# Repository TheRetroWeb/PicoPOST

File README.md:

# PicoPOST

> [!NOTE]
> You can get a quick summary from the blog post! [Introducing the PicoPOST - The Retro Web Blog](https://blog.theretroweb.com/2023/01/03/introducing-the-picopost/)

## Introduction

**PicoPOST** is a PC diagnostic card for systems with, at least, an 8-bit ISA slot. It's based around the Raspberry Pi
Pico, powered by an RP2040.

PicoPOST is designed to provide many additional benefits over the basic POST cards that are commonly available from
Chinese vendors on eBay and other sites.

This project is getting ready for public usage, with a few prototypes already in use for development purposes. More
information soon as it gets finalized.

## Implemented features

- Simple user interface, with a graphical monochrome 128x32 OLED display and a few buttons living on their own remote
  control
- Port 80h readout, with 4-place output history
- Port 90h readout, for IBM PS/2s
- Port 84h reaodut, for Compaq machines*
- Port 300h readout, for some EISA systems*
- Port 378h readout, for some Olivetti machines*
- More complete bus activity dumping facility
- Reset pulse detection
- +5V and +12V ~~and -12V~~ voltage monitor**
- Display is dimmed after 15s of inactivity to mitigate burn-in
- Flying Toasters! screensaver after 30s of inactivity on the main menu

> *: We don't have a specimen handy, so we need confirmation from someone else out there.\
> **: Negative voltages into a positive ADC is too much mental gymnastics without additional hardware

### Videos

We are slowly compiling a [YouTube playlist](https://www.youtube.com/playlist?list=PLejCJef6DKnVJob0ycztrpl9FoBufaOPA)
with a whole bunch of demonstration pieces, showing what the PicoPOST is capable of doing.\
Stay tuned for more content!

### Wishlist

New features have been implemented with the new rev 6 PCB and matching firmware.
- Full bus activity trace (HW OK, FW provisioned, but we need to make sure we are not missing data)
- Bus clock reader (HW OK, FW TBD)
- ... anything else, as long as the hardware allows it and someone implements it in firmware

## Building the firmware

### Automagically

We make use of Visual Studio Code and the official Raspberry Pi Pico extension for an easier life. When you first open
the project in VSCode, you will be prompted to install a few suggested extensions; accept the proposal and follow
on-screen instructions.

You should now be greeted by the CMake and Pi Pico sidebar panels. Use the CMake panel to switch between Debug or
Release builds, then refer to the Pico panel for building, uploading, and debugging the firmware.

It's already set up to probe for a compatible debugger via OpenOCD and gdbserver, and it works really well with our
official Raspberry Pi Debug Probe. I expect other SWD debuggers to work just as well (J-Link, STLink, ...).

### Manually

The firmware is built using the official Raspberry Pi RP2040 SDK. Follow the
[official documentation](https://github.com/raspberrypi/pico-sdk#quick-start-your-own-project) for setting it up.

The procedure is pretty straight-forward:
1. Clone the repo
   ```
   mkdir ~/repo
   cd ~/repo
   git clone https://github.com/TheRetroWeb/PicoPOST
   ```
2. Enter the repo and initialize it
   ```
   cd PicoPOST
   git submodule init
   git submodule update
   ```
3. Prepare the build system with CMake
   ```
   export PICO_SDK_PATH /path/to/pico/sdk
   cmake -DCMAKE_EXPORT_COMPILE_COMMANDS:BOOL=TRUE \
       -DCMAKE_BUILD_TYPE:STRING=Release \
       -DCMAKE_C_COMPILER:FILEPATH=/usr/bin/arm-none-eabi-gcc \
       -DCMAKE_CXX_COMPILER:FILEPATH=/usr/bin/arm-none-eabi-g++ \
       -S./firmware \
       -B./build \
       -G "Unix Makefiles"
   ```
4. Build the firmware
   ```
   cmake --build ./build --config Release --target all -j $(nproc)
   ```

### Customize the firmware

There are a couple of details you might want to tune at compile time. More specifically, you may want to better calibrate
the voltage monitor to show more accurate results.

In the primary `firmware\CMakeLists.txt` file, there are three variables you can set to skew the final ADC conversion result. These were added to account for resistor tolerances in the voltage divider circuits.
- `CALIBADJ_5V`, correction factor for the +5V rail
- `CALIBADJ_12V`, correction factor for the +12V rail

Calculating these factors is pretty straight forward:
- Install the default firmware
- Connect PicoPOST to your computer of choice with a known good power supply
- Enter `Voltage Monitor` mode
- Turn on the computer
- With a multimeter, measure the rail voltage as close as possible to PicoPOST
- Compute the required calibration factor by dividing the measured value with the one shown by PicoPOST
- Edit the `CALIBADJ` variable and build the firmware again

## Flashing the firmware

1. In order to load new firmware, the Pico must be booted into UF2 mode:
   - If the board is powered off, keep the BOOTSEL button pressed while plugging the USB cable into the Pico itself.
   - If the board is already powered, you can short the "Pico Reset" pins on the back of the card instead of removing the USB cable.
   - Alternatively, if the board is powered via USB from a PC with a data cable, you can move to the `Update FW` menu entry. By pressing Enter, the Pico will then be rebooted into UF2 mode automatically.
2. A mass storage device should be now mounted on your computer.
3. Drag and drop (or copy and paste) the `.uf2` firmware file into the device.
4. Once loaded, it will automatically restart and disconnect.
5. If all went well, you should now be greeted by the main menu on the OLED display.\
   You can verify the current firmware version by entering the `Info` page.

## Interested in helping?
- Submit issues and pull requests!
- Join us in the #picopost channel in [The Retro Web discord server](https://discord.gg/TdD4tqQ7fv)
- Join us and other developers of retro Pico hardware (such as PicoGUS and PicoMEM) in the [Retro Pico Hardware discord server](https://discord.gg/QBUkpPqFa5)

## Directories

```
datasheets/  Reference documentation for components used in the PicoPOST
firmware/    Source code for the PicoPOST firmware (written in C/C++ with the official Pico SDK)
pcb/         KiCad schematics and PCB design files
```

## License

The firmware portion of PicoPOST is licensed under the MIT license.\
The hardware portion of PicoPOST is licensed under the CERN OHL v2 Permissive license.

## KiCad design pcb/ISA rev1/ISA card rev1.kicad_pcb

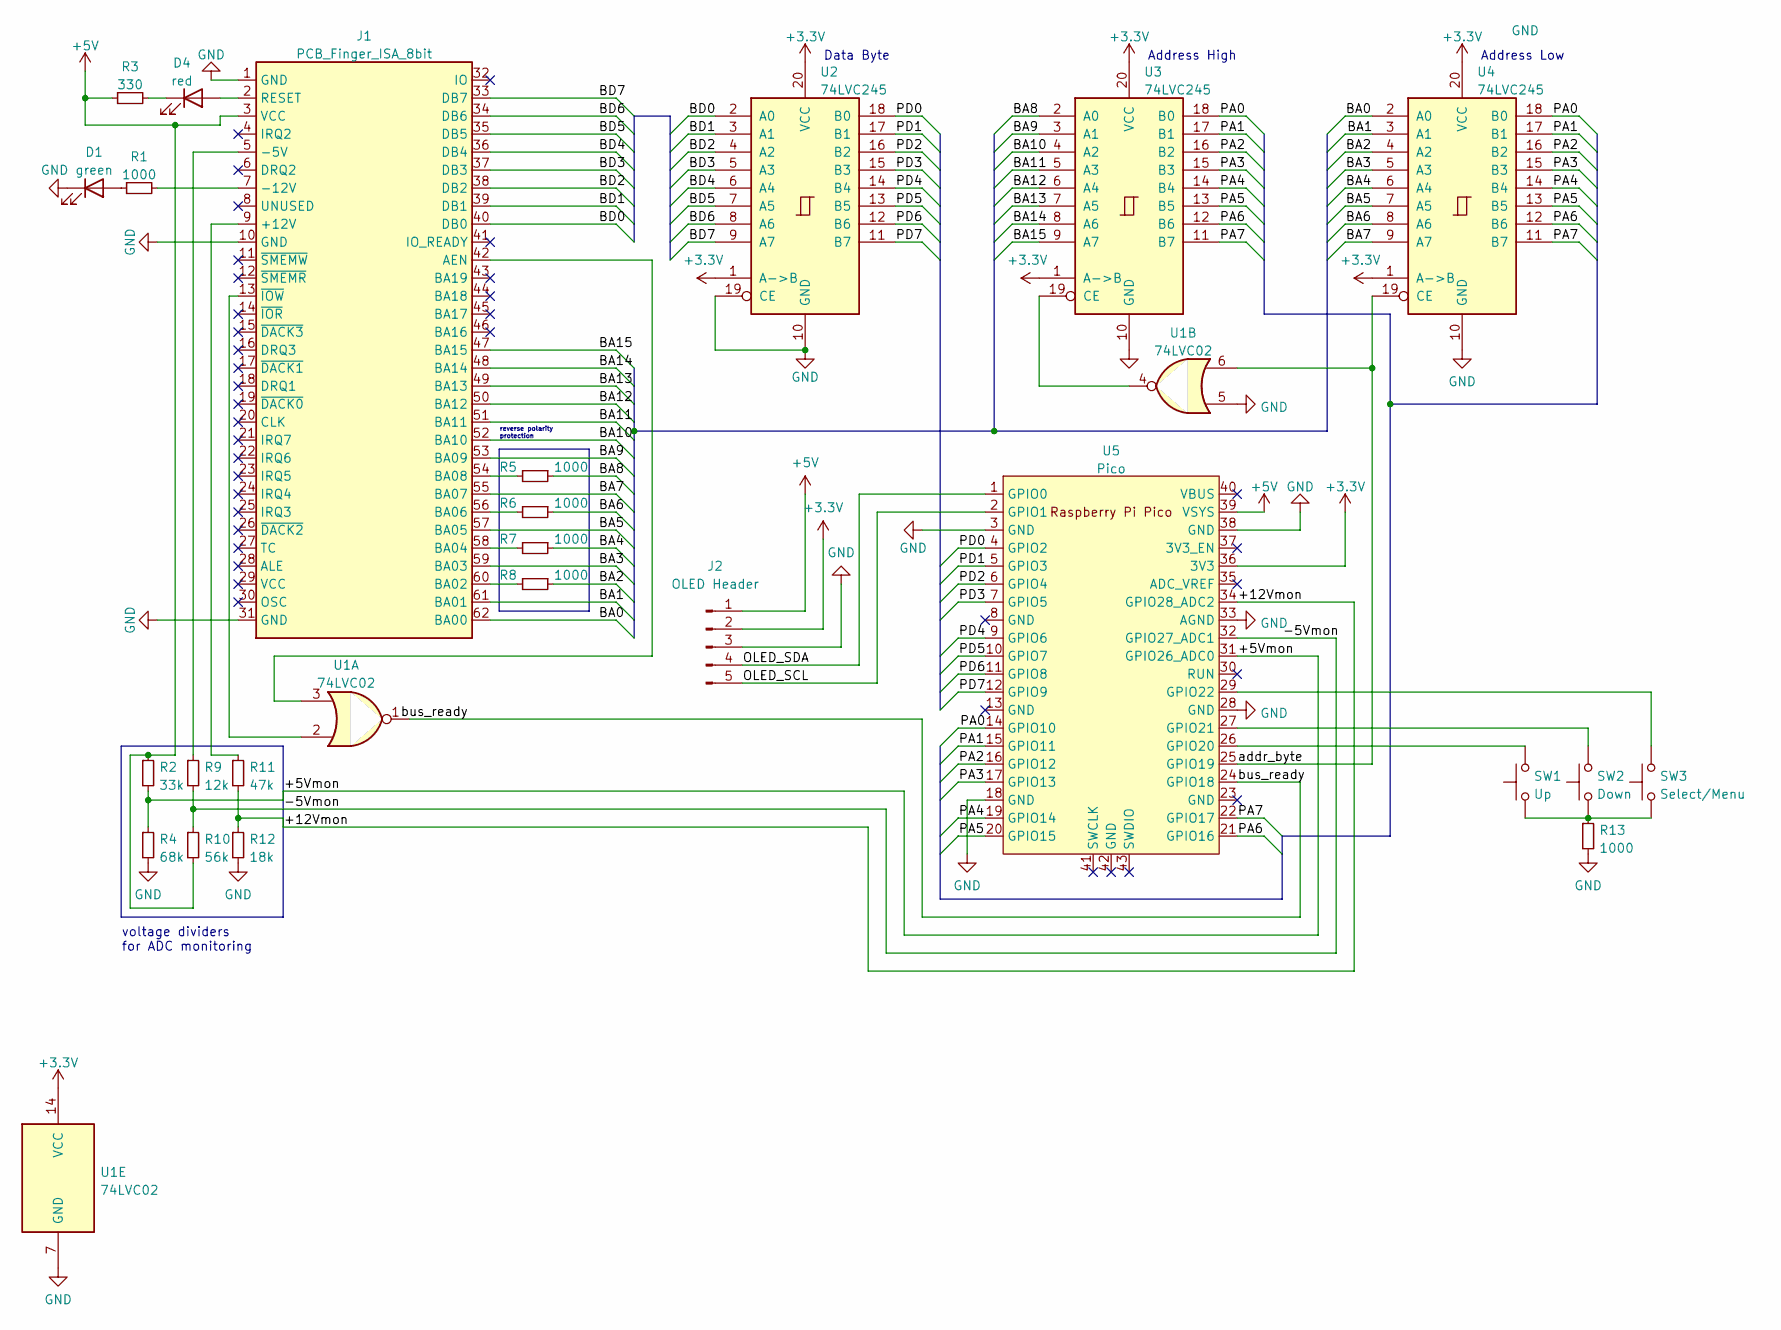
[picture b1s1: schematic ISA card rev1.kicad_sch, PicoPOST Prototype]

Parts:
D1: green; LED_D3.0mm
D4: red; LED_D3.0mm
J1: PCB_Finger_ISA_8bit; BUS_IDE8
J2: OLED Header; PinHeader_1x05_P2.54mm_Vertical
R1, R5, R6, R7, R8, R13: 1000; R_Axial_DIN0207_L6.3mm_D2.5mm_P2.54mm_Vertical
R2: 33k; R_Axial_DIN0207_L6.3mm_D2.5mm_P2.54mm_Vertical
R3: 330; R_Axial_DIN0207_L6.3mm_D2.5mm_P2.54mm_Vertical
R4: 68k; R_Axial_DIN0207_L6.3mm_D2.5mm_P2.54mm_Vertical
R9: 12k; R_Axial_DIN0207_L6.3mm_D2.5mm_P2.54mm_Vertical
R10: 56k; R_Axial_DIN0207_L6.3mm_D2.5mm_P2.54mm_Vertical
R11: 47k; R_Axial_DIN0207_L6.3mm_D2.5mm_P2.54mm_Vertical
R12: 18k; R_Axial_DIN0207_L6.3mm_D2.5mm_P2.54mm_Vertical
SW1: Up; SW_PUSH_6mm_H5mm
SW2: Down; SW_PUSH_6mm_H5mm
SW3: Select/Menu; SW_PUSH_6mm_H5mm
U1: 74LVC02; SO-14_5.3x10.2mm_P1.27mm
U2, U3, U4: 74LVC245; SO-20_5.3x12.6mm_P1.27mm
U5: Pico; RPi_Pico_SMD_TH

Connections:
+3V3: J2.2, U1.14 (VCC), U2.1 (A->B), U2.20 (VCC), U3.1 (A->B), U3.20 (VCC), U4.1 (A->B), U4.20 (VCC), U5.36 (3V3)
+5V: J1.3 (VCC), J2.1, R2.1, R3.1, R10.2, U5.39 (VSYS)
/+5Vmon: R2.2, R4.1, U5.31 (GPIO26_ADC0)
/+12Vmon: R11.2, R12.1, U5.34 (GPIO28_ADC2)
/-5Vmon: R9.2, R10.1, U5.32 (GPIO27_ADC1)
/BA0: J1.62 (BA00), U4.2 (A0)
/BA1: J1.61 (BA01), U4.3 (A1)
/BA2: R8.1, U4.4 (A2)
/BA3: J1.59 (BA03), U4.5 (A3)
/BA4: R7.1, U4.6 (A4)
/BA5: J1.57 (BA05), U4.7 (A5)
/BA6: R6.1, U4.8 (A6)
/BA7: J1.55 (BA07), U4.9 (A7)
/BA8: R5.1, U3.2 (A0)
/BA9: J1.53 (BA09), U3.3 (A1)
/BA10: J1.52 (BA10), U3.4 (A2)
/BA11: J1.51 (BA11), U3.5 (A3)
/BA12: J1.50 (BA12), U3.6 (A4)
/BA13: J1.49 (BA13), U3.7 (A5)
/BA14: J1.48 (BA14), U3.8 (A6)
/BA15: J1.47 (BA15), U3.9 (A7)
/BD0: J1.40 (DB0), U2.2 (A0)
/BD1: J1.39 (DB1), U2.3 (A1)
/BD2: J1.38 (DB2), U2.4 (A2)
/BD3: J1.37 (DB3), U2.5 (A3)
/BD4: J1.36 (DB4), U2.6 (A4)
/BD5: J1.35 (DB5), U2.7 (A5)
/BD6: J1.34 (DB6), U2.8 (A6)
/BD7: J1.33 (DB7), U2.9 (A7)
/OLED_SCL: J2.5, U5.2 (GPIO1)
/OLED_SDA: J2.4, U5.1 (GPIO0)
/PA0: U3.18 (B0), U4.18 (B0), U5.14 (GPIO10)
/PA1: U3.17 (B1), U4.17 (B1), U5.15 (GPIO11)
/PA2: U3.16 (B2), U4.16 (B2), U5.16 (GPIO12)
/PA3: U3.15 (B3), U4.15 (B3), U5.17 (GPIO13)
/PA4: U3.14 (B4), U4.14 (B4), U5.19 (GPIO14)
/PA5: U3.13 (B5), U4.13 (B5), U5.20 (GPIO15)
/PA6: U3.12 (B6), U4.12 (B6), U5.21 (GPIO16)
/PA7: U3.11 (B7), U4.11 (B7), U5.22 (GPIO17)
/PD0: U2.18 (B0), U5.4 (GPIO2)
/PD1: U2.17 (B1), U5.5 (GPIO3)
/PD2: U2.16 (B2), U5.6 (GPIO4)
/PD3: U2.15 (B3), U5.7 (GPIO5)
/PD4: U2.14 (B4), U5.9 (GPIO6)
/PD5: U2.13 (B5), U5.10 (GPIO7)
/PD6: U2.12 (B6), U5.11 (GPIO8)
/PD7: U2.11 (B7), U5.12 (GPIO9)
/addr_byte: U1.6, U4.19 (CE), U5.25 (GPIO19)
/bus_ready: U1.1, U5.24 (GPIO18)
GND: D1.1 (K), J1.1 (GND), J1.10 (GND), J1.31 (GND), J2.3, R4.2, R12.2, R13.2, U1.5, U1.7 (GND), U2.10 (GND), U2.19 (CE), U3.10 (GND), U4.10 (GND), U5.3 (GND), U5.18 (GND), U5.28 (GND), U5.33 (AGND), U5.38 (GND)
unnamed: D1.2 (A), R1.1
unnamed: D4.1 (K), R3.2
unnamed: D4.2 (A), J1.2 (RESET)
unnamed: J1.5 (-5V), R9.1
unnamed: J1.7 (-12V), R1.2
unnamed: J1.9 (+12V), R11.1
unnamed: J1.13 (~IOW), U1.2
unnamed: J1.42 (AEN), U1.3
unnamed: J1.54 (BA08), R5.2
unnamed: J1.56 (BA06), R6.2
unnamed: J1.58 (BA04), R7.2
unnamed: J1.60 (BA02), R8.2
unnamed: R13.1, SW1.1, SW2.1, SW3.1
unnamed: U1.4, U3.19 (CE)
unnamed: SW1.2, U5.26 (GPIO20)
unnamed: SW2.2, U5.27 (GPIO21)
unnamed: SW3.2, U5.29 (GPIO22)

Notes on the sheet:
reverse polarity protection
Data Byte
Address High
Address Low
voltage dividers for ADC monitoring

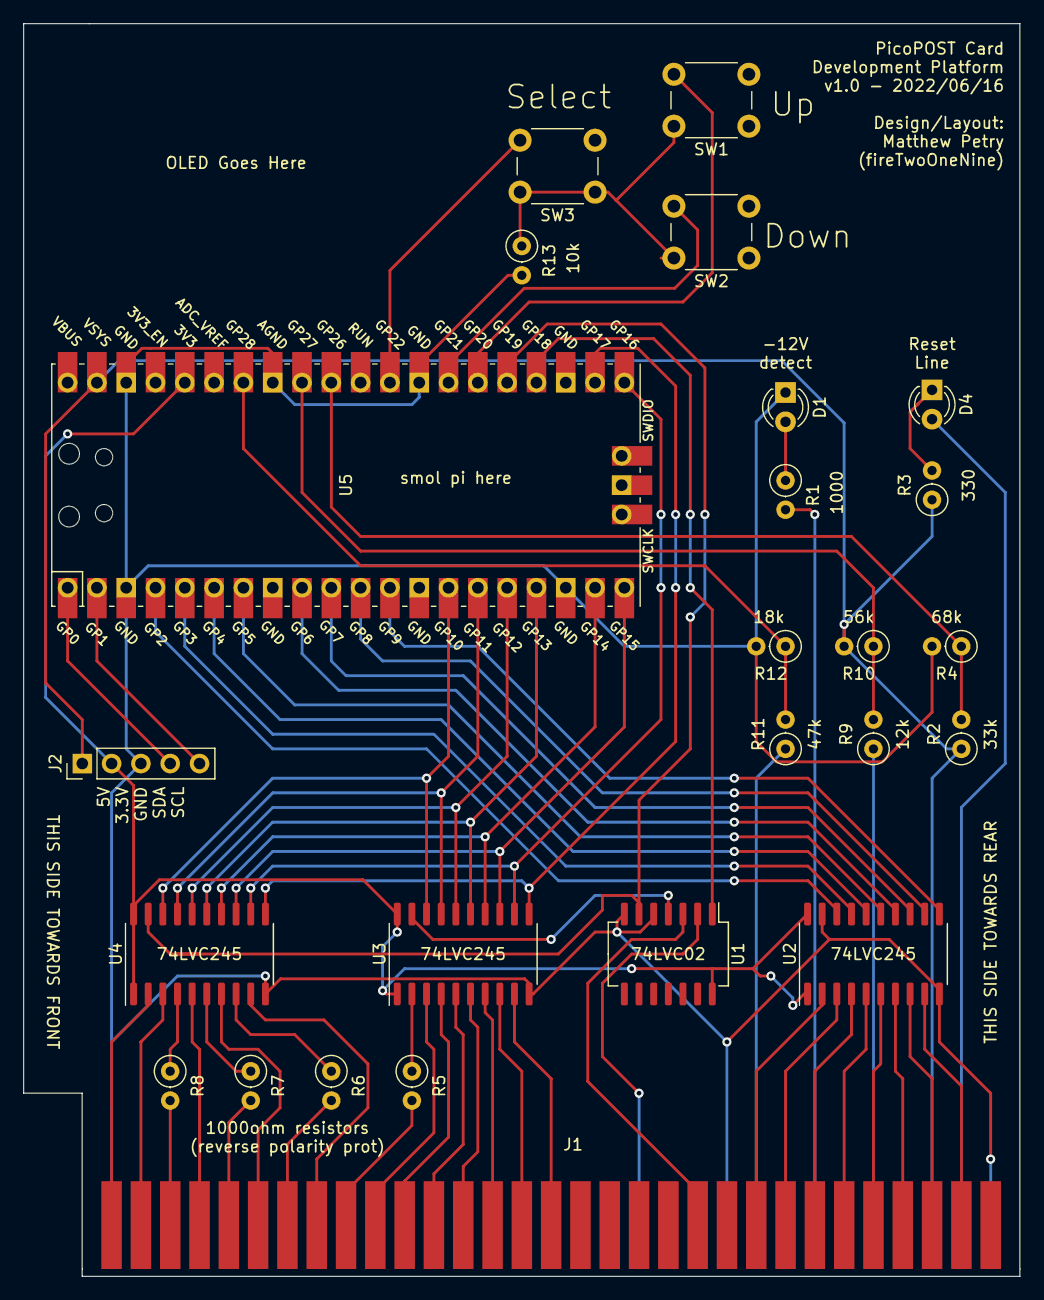
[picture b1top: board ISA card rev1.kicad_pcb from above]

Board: 2 copper layers, 86.4 x 108.6 mm, 25 parts (0 on the bottom side), 67 nets.

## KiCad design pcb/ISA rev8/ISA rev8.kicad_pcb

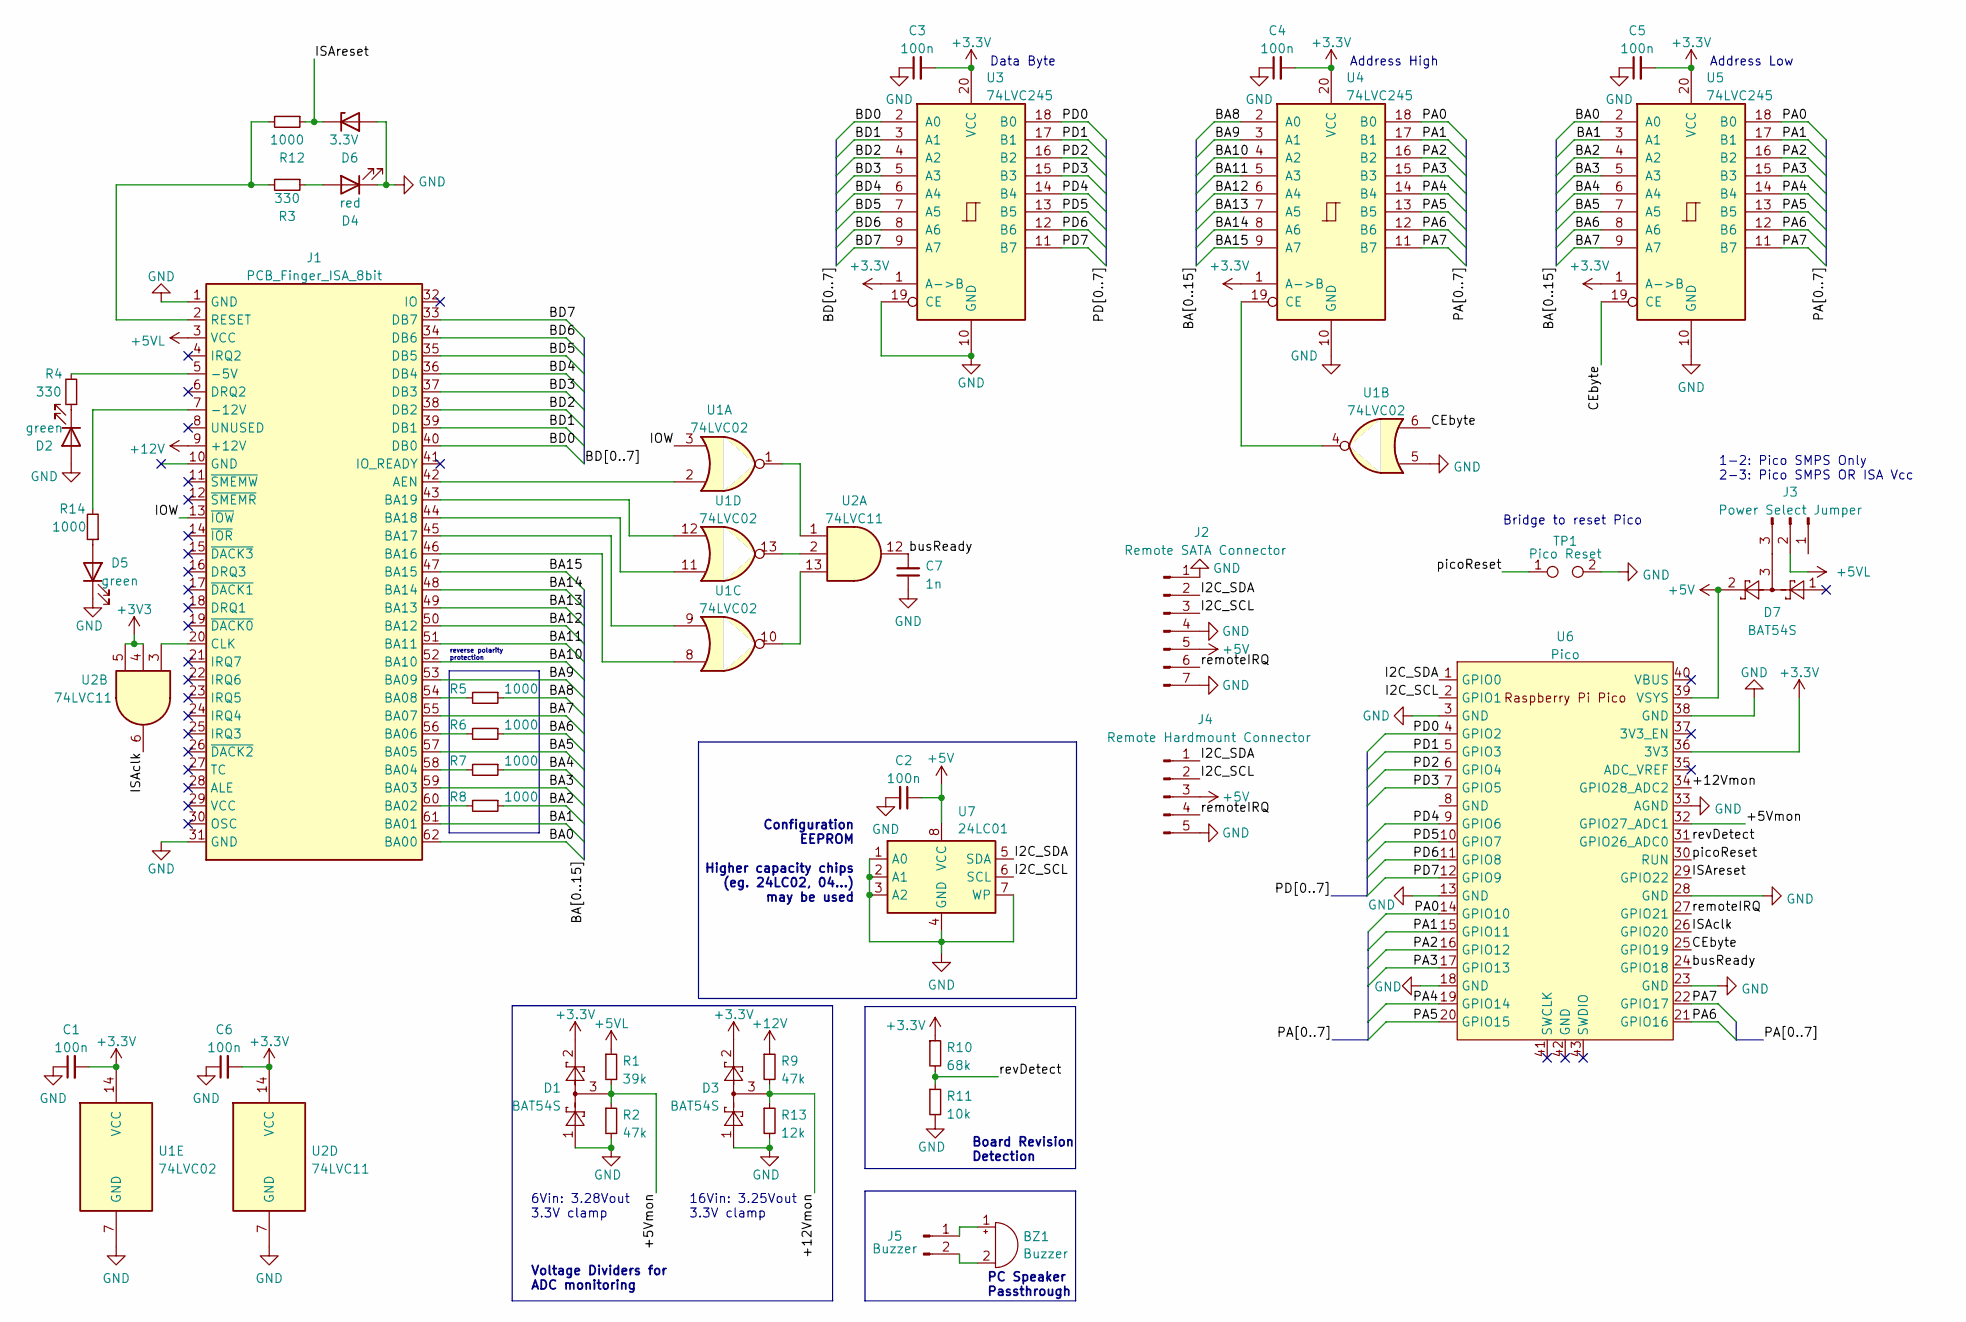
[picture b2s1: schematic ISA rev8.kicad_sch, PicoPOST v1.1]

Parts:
BZ1: Buzzer; 7.6mm side mount buzzer
C1, C2, C3, C4, C5, C6: 100n; C_1206_3216Metric_Pad1.33x1.80mm_HandSolder
C7: 1n; C_1206_3216Metric_Pad1.33x1.80mm_HandSolder
D1, D3, D7: BAT54S; SOT-23_Handsoldering
D2, D5: green; LED_D3.0mm
D4: red; LED_D3.0mm
D6: 3.3V; TO-236AB_diode
J1: PCB_Finger_ISA_8bit; BUS_IDE8
J2: Remote SATA Connector; Molex-47080-4001-0-0-0
J3: Power Select Jumper; PinHeader_1x03_P2.54mm_Vertical
J4: Remote Hardmount Connector; PinHeader_1x05_P2.54mm_Horizontal
J5: Buzzer; PinHeader_1x02_P2.54mm_Vertical
R1: 39k; R_1206_3216Metric_Pad1.30x1.75mm_HandSolder
R2, R9: 47k; R_1206_3216Metric_Pad1.30x1.75mm_HandSolder
R3, R4: 330; R_1206_3216Metric_Pad1.30x1.75mm_HandSolder
R5, R6, R7, R8, R12, R14: 1000; R_1206_3216Metric_Pad1.30x1.75mm_HandSolder
R10: 68k; R_1206_3216Metric_Pad1.30x1.75mm_HandSolder
R11: 10k; R_1206_3216Metric_Pad1.30x1.75mm_HandSolder
R13: 12k; R_1206_3216Metric_Pad1.30x1.75mm_HandSolder
TP1: Pico Reset; 6mm single side button
U1: 74LVC02; SO-14_3.9x8.65mm_P1.27mm
U2: 74LVC11; SO-14_3.9x8.65mm_P1.27mm
U3, U4, U5: 74LVC245; SO-20_5.3x12.6mm_P1.27mm
U6: Pico; RPi_Pico_SMD_TH
U7: 24LC01; SOIC-8_3.9x4.9mm_P1.27mm

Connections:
+5V: C2.1, D7.2, J2.5, J4.3, U6.39 (VSYS), U7.8 (VCC)
+5VL: J1.3 (VCC), J3.2, R1.1
+12V: J1.9 (+12V), R9.1
/+5Vmon: D1.3, R1.2, R2.1, U6.32 (GPIO27_ADC1)
/+12Vmon: D3.3, R9.2, R13.1, U6.34 (GPIO28_ADC2)
/BA0: J1.62 (BA00), U5.2 (A0)
/BA1: J1.61 (BA01), U5.3 (A1)
/BA2: R8.1, U5.4 (A2)
/BA3: J1.59 (BA03), U5.5 (A3)
/BA4: R7.1, U5.6 (A4)
/BA5: J1.57 (BA05), U5.7 (A5)
/BA6: R6.1, U5.8 (A6)
/BA7: J1.55 (BA07), U5.9 (A7)
/BA8: R5.1, U4.2 (A0)
/BA9: J1.53 (BA09), U4.3 (A1)
/BA10: J1.52 (BA10), U4.4 (A2)
/BA11: J1.51 (BA11), U4.5 (A3)
/BA12: J1.50 (BA12), U4.6 (A4)
/BA13: J1.49 (BA13), U4.7 (A5)
/BA14: J1.48 (BA14), U4.8 (A6)
/BA15: J1.47 (BA15), U4.9 (A7)
/BD0: J1.40 (DB0), U3.2 (A0)
/BD1: J1.39 (DB1), U3.3 (A1)
/BD2: J1.38 (DB2), U3.4 (A2)
/BD3: J1.37 (DB3), U3.5 (A3)
/BD4: J1.36 (DB4), U3.6 (A4)
/BD5: J1.35 (DB5), U3.7 (A5)
/BD6: J1.34 (DB6), U3.8 (A6)
/BD7: J1.33 (DB7), U3.9 (A7)
/CEbyte: U1.6, U5.19 (CE), U6.25 (GPIO19)
/I2C_SCL: J2.3, J4.2, U6.2 (GPIO1), U7.6 (SCL)
/I2C_SDA: J2.2, J4.1, U6.1 (GPIO0), U7.5 (SDA)
/IOW: J1.13 (~IOW), U1.3
/ISAclk: U2.6, U6.26 (GPIO20)
/ISAreset: D6.1 (K), R12.1, U6.29 (GPIO22)
/PA0: U4.18 (B0), U5.18 (B0), U6.14 (GPIO10)
/PA1: U4.17 (B1), U5.17 (B1), U6.15 (GPIO11)
/PA2: U4.16 (B2), U5.16 (B2), U6.16 (GPIO12)
/PA3: U4.15 (B3), U5.15 (B3), U6.17 (GPIO13)
/PA4: U4.14 (B4), U5.14 (B4), U6.19 (GPIO14)
/PA5: U4.13 (B5), U5.13 (B5), U6.20 (GPIO15)
/PA6: U4.12 (B6), U5.12 (B6), U6.21 (GPIO16)
/PA7: U4.11 (B7), U5.11 (B7), U6.22 (GPIO17)
/PD0: U3.18 (B0), U6.4 (GPIO2)
/PD1: U3.17 (B1), U6.5 (GPIO3)
/PD2: U3.16 (B2), U6.6 (GPIO4)
/PD3: U3.15 (B3), U6.7 (GPIO5)
/PD4: U3.14 (B4), U6.9 (GPIO6)
/PD5: U3.13 (B5), U6.10 (GPIO7)
/PD6: U3.12 (B6), U6.11 (GPIO8)
/PD7: U3.11 (B7), U6.12 (GPIO9)
/busReady: C7.2, U2.12, U6.24 (GPIO18)
/picoReset: TP1.1, U6.30 (RUN)
/remoteIRQ: J2.6, J4.4, U6.27 (GPIO21)
/revDetect: R10.2, R11.1, U6.31 (GPIO26_ADC0)
GND: C1.1, C2.2, C3.1, C4.1, C5.1, C6.1, C7.1, D1.1, D2.2 (A), D3.1, D4.1 (K), D5.1 (K), D6.2 (A), J1.1 (GND), J1.31 (GND), J2.1, J2.4, J2.7, J4.5, R2.2, R11.2, R13.2, TP1.2, U1.5, U1.7 (GND), U2.7 (GND), U3.10 (GND), U3.19 (CE), U4.10 (GND), U5.10 (GND), U6.3 (GND), U6.13 (GND), U6.18 (GND), U6.23 (GND), U6.28 (GND), U6.33 (AGND), U6.38 (GND), U7.1 (A0), U7.2 (A1), U7.3 (A2), U7.4 (GND), U7.7 (WP)
unnamed: BZ1.2 (+), J5.2
unnamed: BZ1.1 (-), J5.1
unnamed: D2.1 (K), R4.1
unnamed: D4.2 (A), R3.1
unnamed: D5.2 (A), R14.1
unnamed: J1.5 (-5V), R4.2
unnamed: J1.7 (-12V), R14.2
unnamed: J1.42 (AEN), U1.2
unnamed: J1.60 (BA02), R8.2
unnamed: J1.58 (BA04), R7.2
unnamed: J1.56 (BA06), R6.2
unnamed: J1.54 (BA08), R5.2
unnamed: J1.46 (BA16), U1.8
unnamed: J1.45 (BA17), U1.9
unnamed: J1.44 (BA18), U1.11
unnamed: J1.43 (BA19), U1.12
unnamed: J1.20 (CLK), U2.3
unnamed: J1.2 (RESET), R3.2, R12.2
unnamed: D7.3, J3.3
unnamed: U1.1, U2.1
unnamed: U1.10, U2.13
unnamed: U1.13, U2.2
unnamed: U1.4, U4.19 (CE)

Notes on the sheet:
6Vin: 3.28Vout 3.3V clamp
Configuration EEPROM Higher capacity chips (eg. 24LC02, 04...) may be used
Board Revision Detection
Voltage Dividers for ADC monitoring
reverse polarity protection
Data Byte
Bridge to reset Pico
Address High
1-2: Pico SMPS Only 2-3: Pico SMPS OR ISA Vcc
PC Speaker Passthrough
Address Low
16Vin: 3.25Vout 3.3V clamp

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
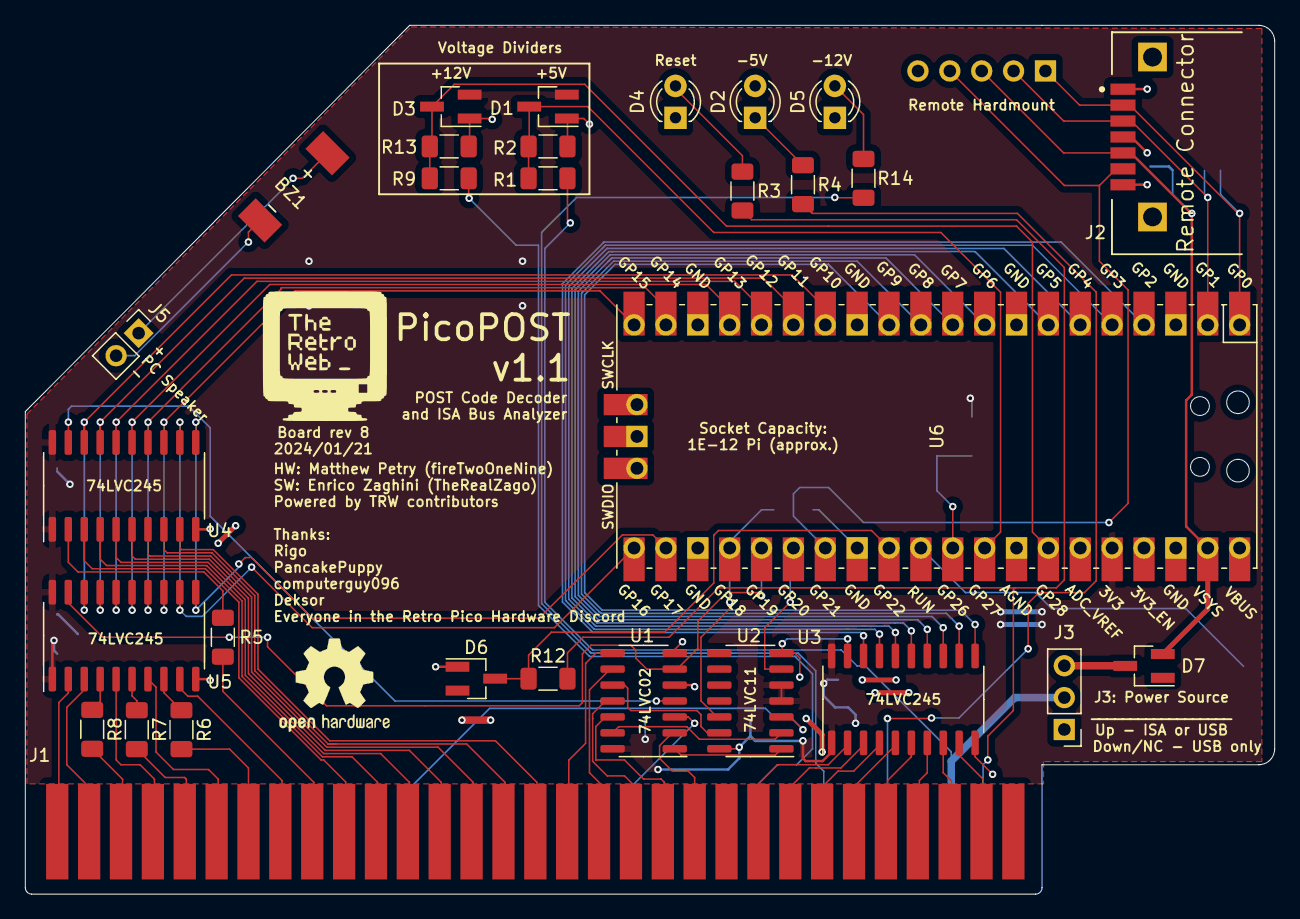
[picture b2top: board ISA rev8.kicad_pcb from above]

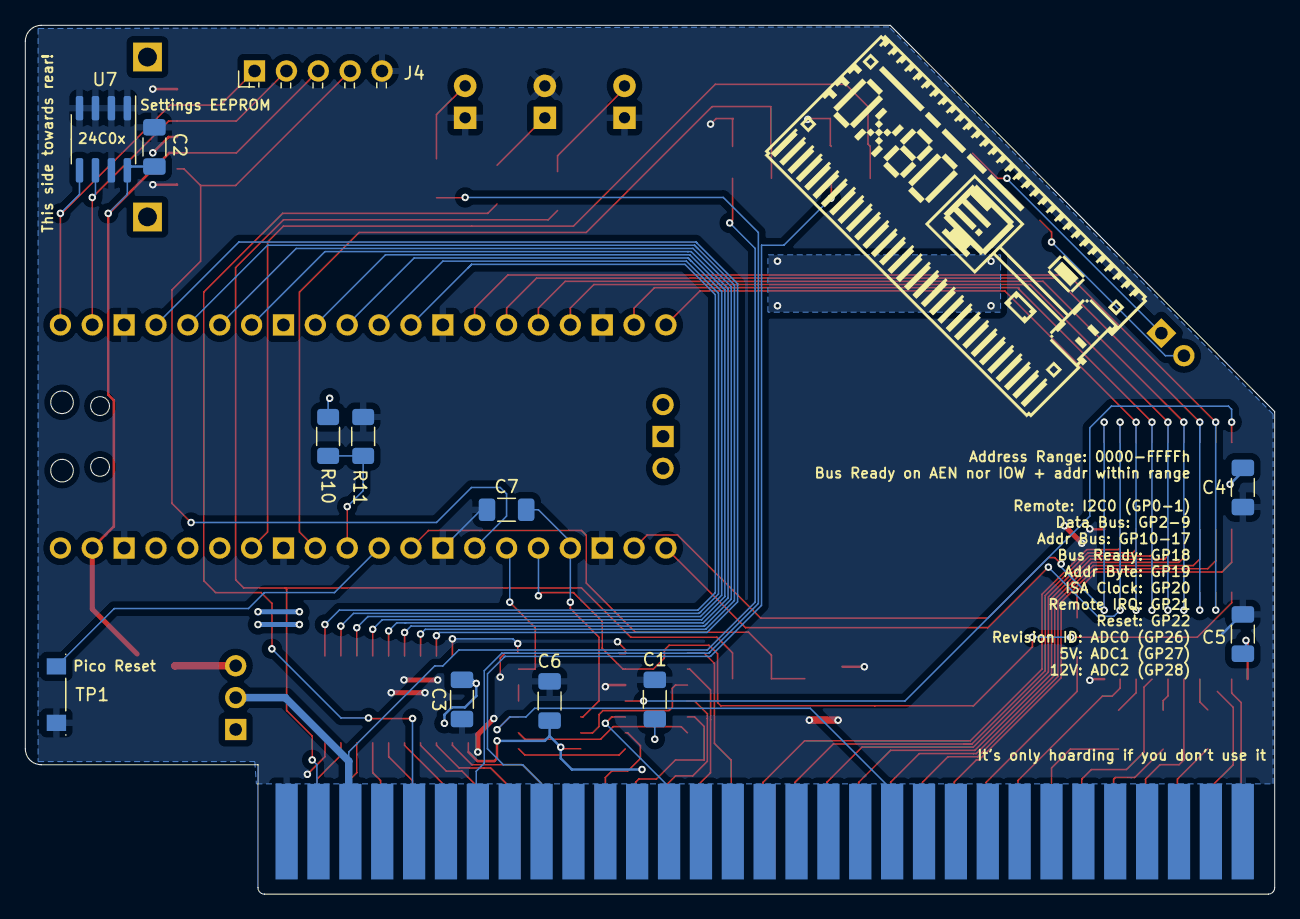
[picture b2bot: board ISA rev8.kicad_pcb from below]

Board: 2 copper layers, 99.6 x 69.2 mm, 43 parts (13 on the bottom side), 80 nets.

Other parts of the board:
.: LOGO; picopost_logo

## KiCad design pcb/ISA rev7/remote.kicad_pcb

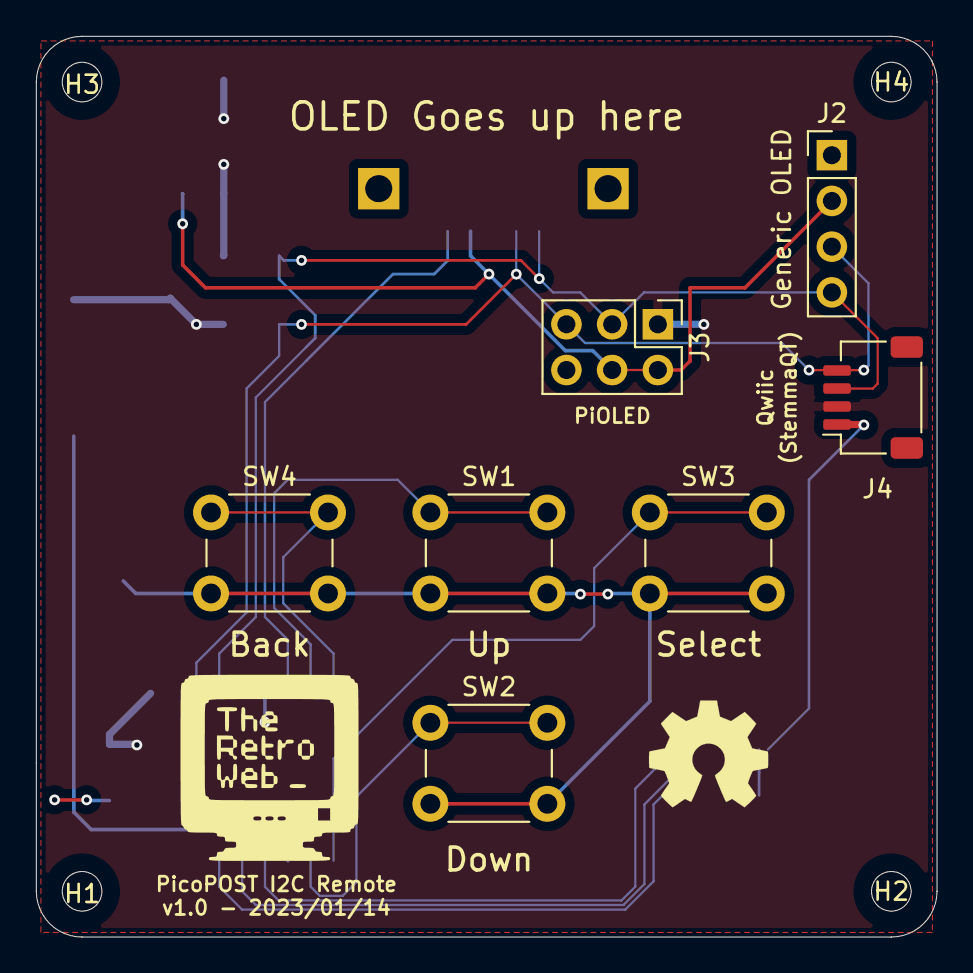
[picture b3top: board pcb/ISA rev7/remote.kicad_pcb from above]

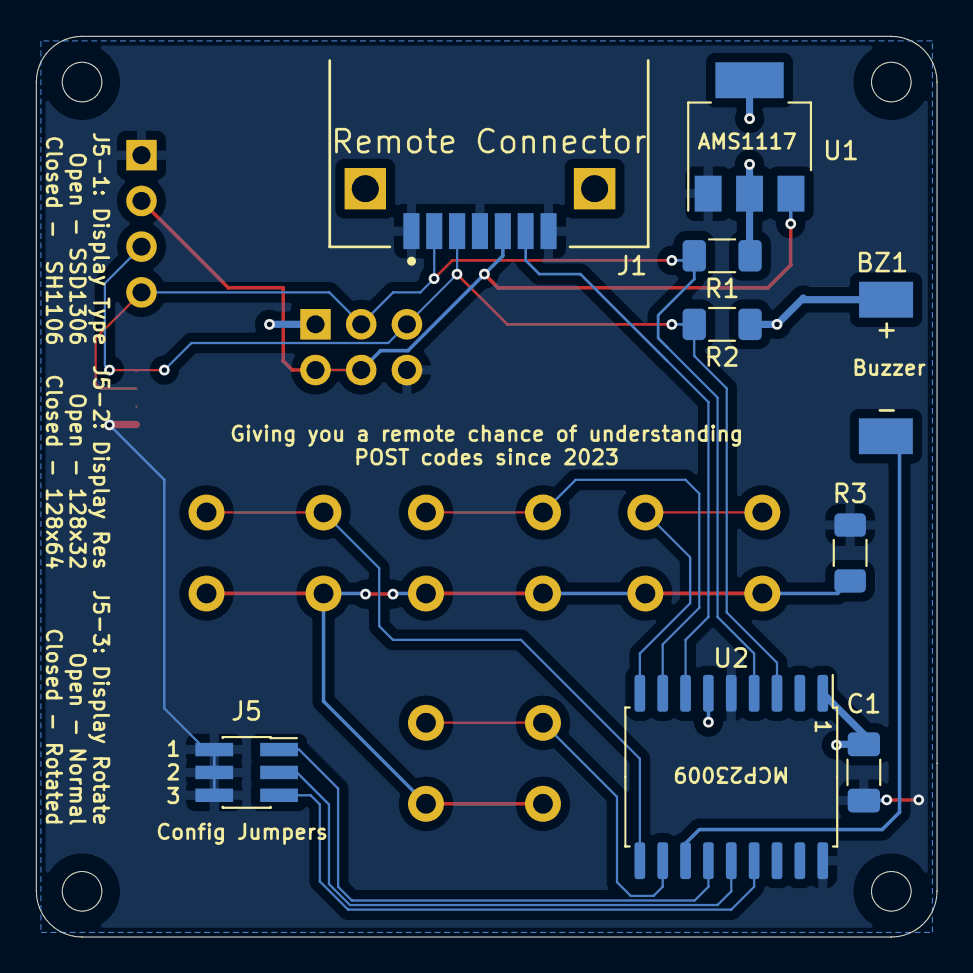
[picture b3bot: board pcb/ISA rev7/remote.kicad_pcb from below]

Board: 2 copper layers, 50.0 x 50.0 mm, 20 parts (9 on the bottom side), 15 nets.

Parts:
BZ1: Buzzer; 7.6mm side mount buzzer
C1: 100n; C_1206_3216Metric_Pad1.33x1.80mm_HandSolder
H1, H2, H3, H4: MountingHole; MountingHole_2.2mm_M2
J1: Remote Connector; Molex-47080-4001-0-0-0
J2: Generic Connector; PinHeader_1x04_P2.54mm_Vertical
J3: PiOLED Connector; PinHeader_2x03_P2.54mm_Vertical
J4: Qwiic/STEMMA QT; JST_SH_SM04B-SRSS-TB_1x04-1MP_P1.00mm_Horizontal
J5: Config Jumpers; PinSocket_2x03_P1.27mm_Vertical_SMD
R1, R2, R3: 1000; R_1206_3216Metric_Pad1.30x1.75mm_HandSolder
SW1: Up; SW_PUSH_6mm
SW2: Down; SW_PUSH_6mm
SW3: Select; SW_PUSH_6mm
SW4: Back; SW_PUSH_6mm
U1: AMS1117-3.3; SOT-223-3_TabPin2
U2: MCP23009-SO; SOIC-18W_7.5x11.6mm_P1.27mm

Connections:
+3V3: BZ1.1 (-), C1.1, J3.1, J4.2, R1.1, R2.1, U1.2 (VO), U2.1 (VDD), U2.6 (~RESET)
+5V: J1.5, J2.2, J3.2, J3.4, U1.3 (VI)
/IRQ: J1.6, U2.7 (INT)
/SCL: J1.3, J2.3, J3.5, J4.4, R2.2, U2.3 (SCL)
/SDA: J1.2, J2.4, J3.3, J4.3, R1.2, U2.4 (SDA)
GND: C1.2, J1.1, J1.4, J1.7, J2.1, J3.6, J4.1, J5.2, J5.4, J5.6, R3.1, U1.1 (GND), U2.5 (ADDR), U2.18 (VSS)
unnamed: BZ1.2 (+), U2.12 (GP4)
unnamed: J5.1, U2.13 (GP5)
unnamed: J5.3, U2.14 (GP6)
unnamed: J5.5, U2.15 (GP7)
unnamed: R3.2, SW1.2, SW2.2, SW3.2, SW4.2
unnamed: SW1.1, U2.8 (GP0)
unnamed: SW2.1, U2.11 (GP3)
unnamed: SW3.1, U2.10 (GP2)
unnamed: SW4.1, U2.9 (GP1)

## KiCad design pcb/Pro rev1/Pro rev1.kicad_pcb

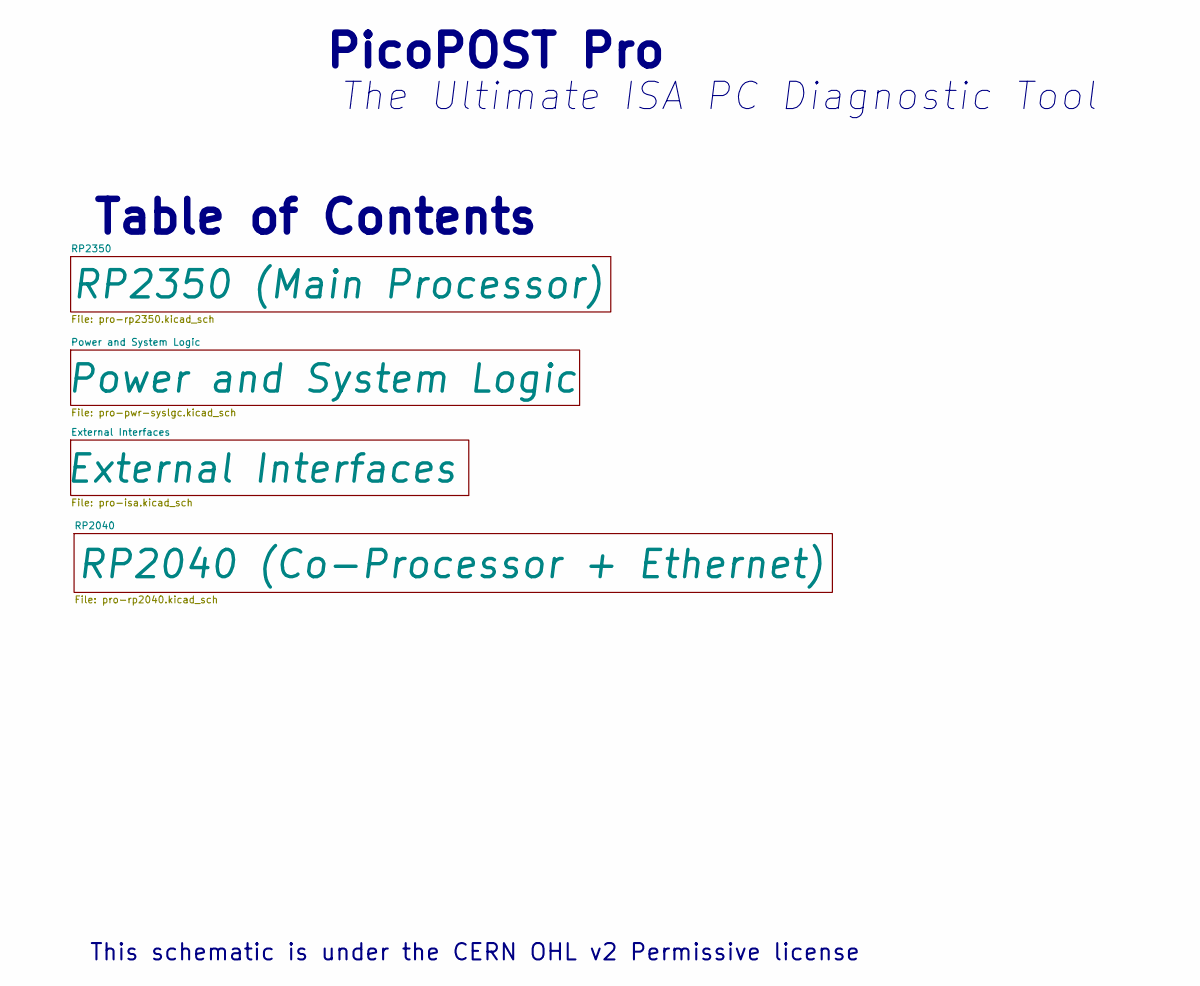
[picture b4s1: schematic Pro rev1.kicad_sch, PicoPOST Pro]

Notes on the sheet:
The Ultimate ISA PC Diagnostic Tool
This schematic is under the CERN OHL v2 Permissive license
PicoPOST Pro
Table of Contents
